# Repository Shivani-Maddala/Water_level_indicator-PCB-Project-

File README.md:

# Water_level_indicator_PCB-Project
This repository contains a Water Level Indicator PCB designed using KiCad. The circuit helps monitor water levels in a tank and provides alerts to prevent overflow or dry-run conditions. The project includes schematic and PCB design files

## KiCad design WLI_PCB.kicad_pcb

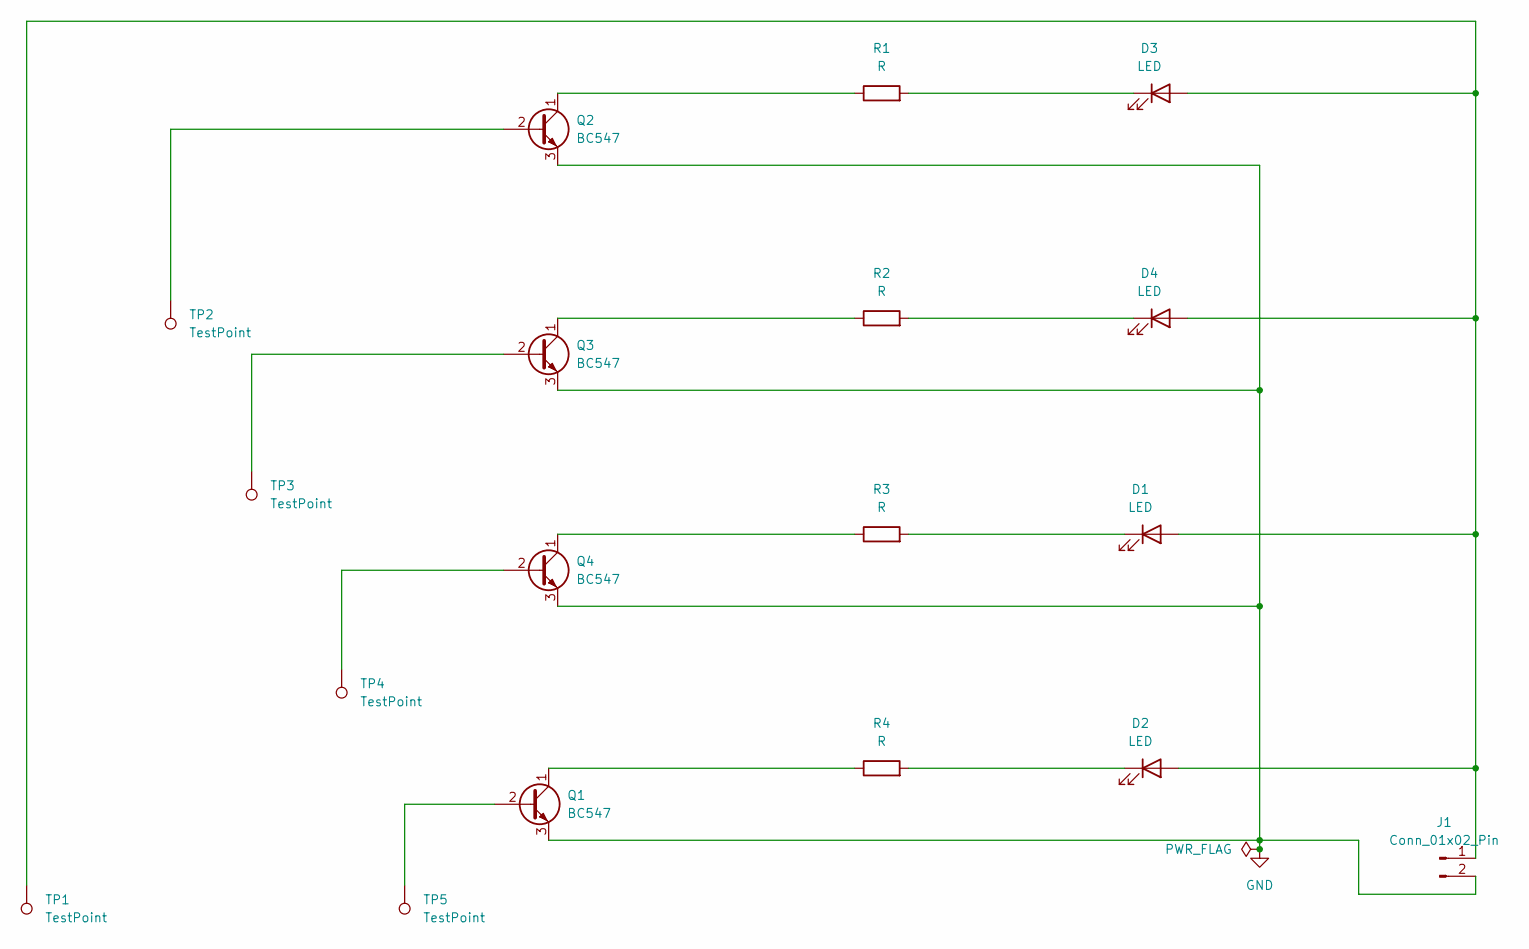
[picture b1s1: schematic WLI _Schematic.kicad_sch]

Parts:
D1, D2, D3, D4: LED; LED_D5.0mm_IRBlack
J1: Conn_01x02_Pin; JWT_A3963_1x02_P3.96mm_Vertical
Q1, Q2, Q3, Q4: BC547; TO-92_Inline_Wide
R1, R2, R3, R4: R; R_Axial_DIN0207_L6.3mm_D2.5mm_P10.16mm_Horizontal
TP1, TP2, TP3, TP4, TP5: TestPoint; TestPoint_Pad_D3.0mm

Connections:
GND: J1.2, Q1.3 (E), Q2.3 (E), Q3.3 (E), Q4.3 (E)
unnamed: D1.2 (A), D2.2 (A), D3.2 (A), D4.2 (A), J1.1, TP1.1
unnamed: D1.1 (K), R3.2
unnamed: D2.1 (K), R4.2
unnamed: D3.1 (K), R1.2
unnamed: D4.1 (K), R2.2
unnamed: Q1.2 (B), TP5.1
unnamed: Q1.1 (C), R4.1
unnamed: Q2.2 (B), TP2.1
unnamed: Q2.1 (C), R1.1
unnamed: Q3.2 (B), TP3.1
unnamed: Q3.1 (C), R2.1
unnamed: Q4.2 (B), TP4.1
unnamed: Q4.1 (C), R3.1

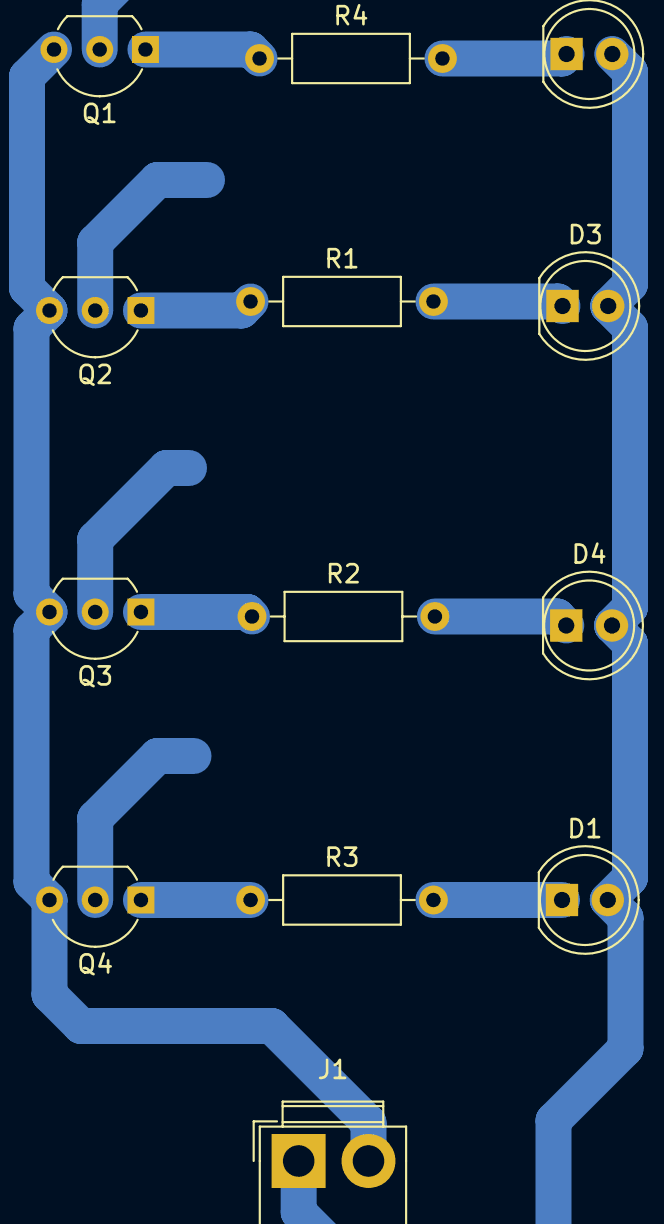
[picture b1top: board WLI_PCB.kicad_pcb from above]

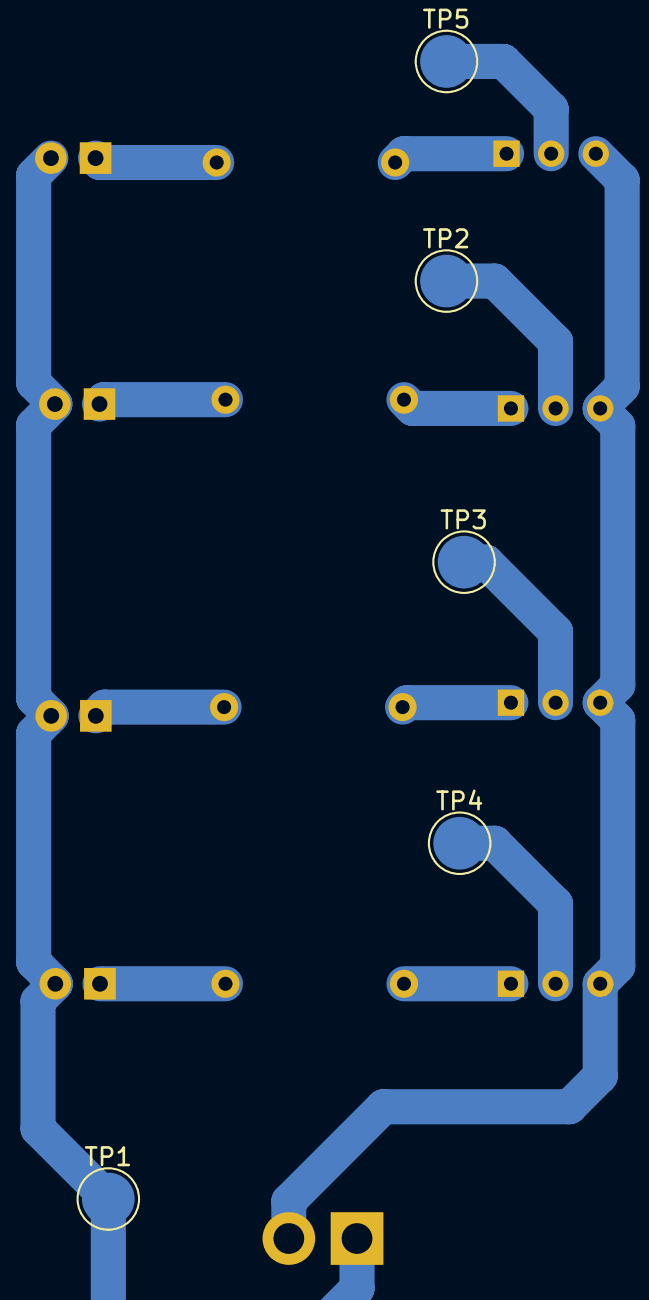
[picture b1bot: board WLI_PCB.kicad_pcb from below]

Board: 2 copper layers, 18 parts (5 on the bottom side), 14 nets.
